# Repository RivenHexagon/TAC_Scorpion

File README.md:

# TAC_Scorpion
## Mixing Console S1100 Channel Modification

This modification **splits** the TAC Scorpion **S1100** channel **modules** into three **groups** and **modifies** them accordingly:

*   **Group 1**: AML-16-007 ***Mic Input*** Modification<br>
    <http://www.audiomaintenance.com/acatalog/AML-16-007_extended_info.html>
*   **Group 2**: AML-16-004 ***Line Input*** Modification<br>
    <http://www.audiomaintenance.com/acatalog/AML-16-004_extended_info.html>
*   **Group 3**: SK25 ***Descrete Op-Amp*** (DOA) Modification<br>
    <https://www.soundskulptor.com/en/proddetail.php?prod=SK25>

### New Circuit Diagrams
For each modification the **circuit diagram** of the **S1100** module (PBC GL270D) is **redrawn**, reflecting the changes made.

### New Connector Cards
Further more, all **connector cards** are **redesigned**, providing a single layer **PCB layout** for **DIY** manuafcturing. It has slight improvements and allowes for the replacement of old **corroded** connectors with **new** gold plated components.

### This Repo
This repository provides all the **design resources** created for this project. The majority of the modifications are **based** on the reverse engineering of the above linked **Audio Maintenance Limited** products and the **Sound Sculptor** kit.

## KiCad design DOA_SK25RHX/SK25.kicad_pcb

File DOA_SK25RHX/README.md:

## Soundskulptor SK 25
<https://www.soundskulptor.com/en/proddetail.php?prod=SK25>
The SK25 Descrete OpAmp module is redesigned with our own layout for DIY process.

### AMEK/TAC Scorpion 2520 Differential Mod

<https://www.pcbway.com/project/share/AMEK_TAC_Scorpion_2520_Differential_Mod___.html>

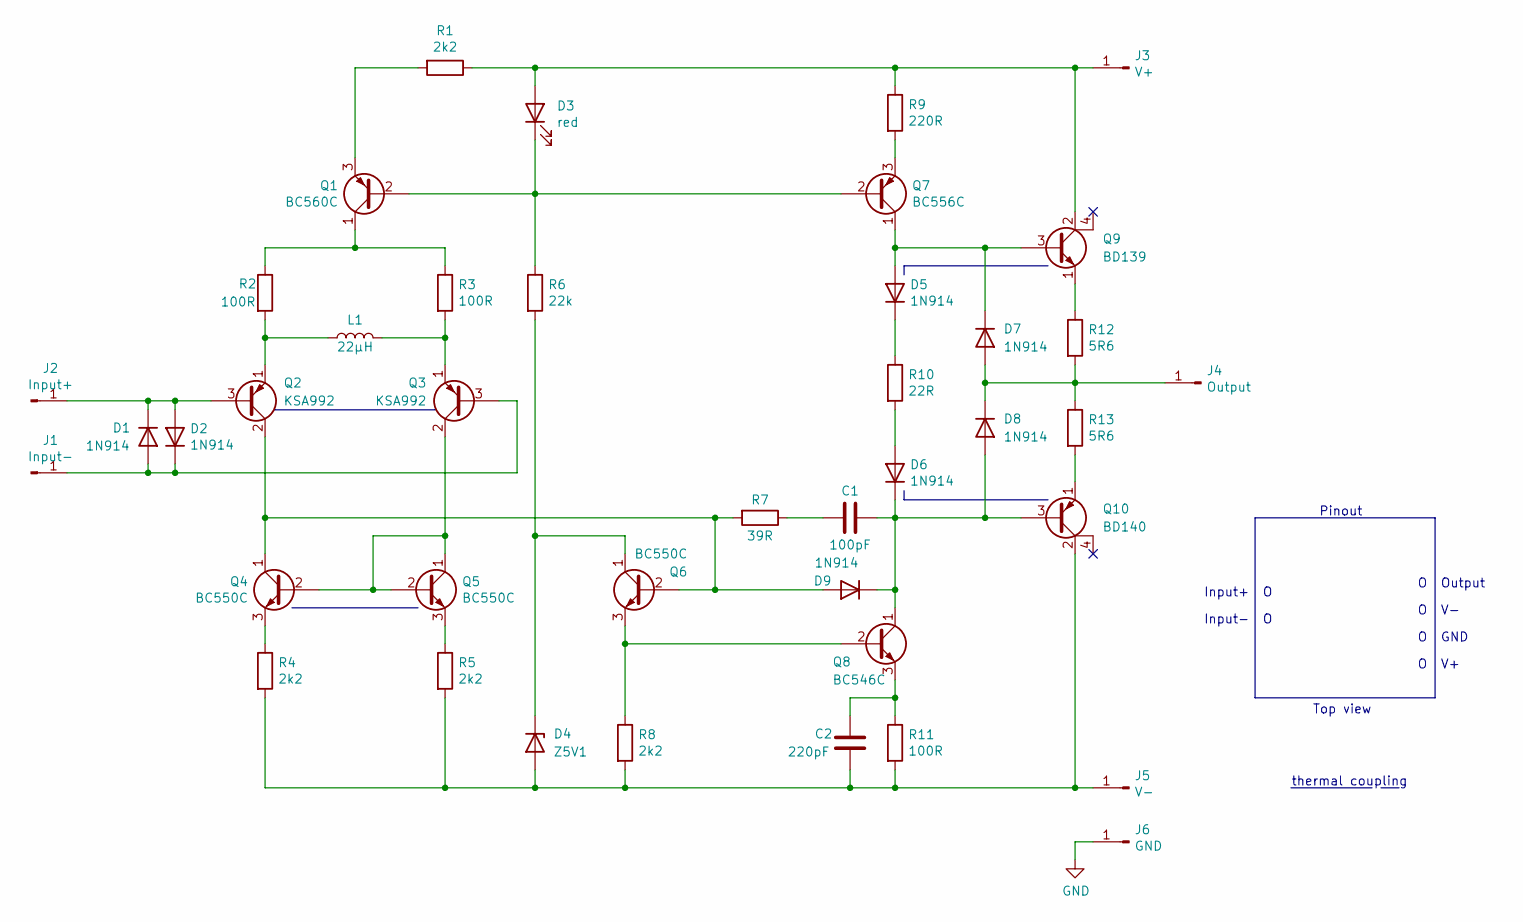
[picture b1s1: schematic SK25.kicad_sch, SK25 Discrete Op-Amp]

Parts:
C1: 100pF; C_Disc_D5.0mm_W2.5mm_P2.50mm
C2: 220pF; C_Disc_D5.0mm_W2.5mm_P2.50mm
D1, D2, D7, D8, D9: 1N914; D_DO-35_SOD27_P2.54mm_Vertical_KathodeUp
D3: red; LED_D3.0mm
D4: Z5V1; D_DO-35_SOD27_P2.54mm_Vertical_AnodeUp
D5, D6: 1N914; D_DO-35_SOD27_P10.16mm_Horizontal
J1: Input-; Pin_D1.1mm_L8.5mm_W2.5mm_FlatFork
J2: Input+; Pin_D1.1mm_L8.5mm_W2.5mm_FlatFork
J3: V+; Pin_D1.1mm_L8.5mm_W2.5mm_FlatFork
J4: Output; Pin_D1.1mm_L8.5mm_W2.5mm_FlatFork
J5: V-; Pin_D1.1mm_L8.5mm_W2.5mm_FlatFork
J6: GND; Pin_D1.1mm_L8.5mm_W2.5mm_FlatFork
L1: 22µH; L_Axial_L6.6mm_D2.7mm_P2.54mm_Vertical_Vishay_IM-2
Q1: BC560C; TO-92
Q2, Q3: KSA992; TO-92
Q4, Q5, Q6: BC550C; TO-92
Q7: BC556C; TO-92
Q8: BC546C; TO-92
Q9: BD139; to225_std
Q10: BD140; to225_std
R1, R4, R5, R8: 2k2; R_Axial_DIN0207_L6.3mm_D2.5mm_P2.54mm_Vertical
R2, R3, R11: 100R; R_Axial_DIN0207_L6.3mm_D2.5mm_P2.54mm_Vertical
R6: 22k; R_Axial_DIN0207_L6.3mm_D2.5mm_P2.54mm_Vertical
R7: 39R; R_Axial_DIN0207_L6.3mm_D2.5mm_P2.54mm_Vertical
R9: 220R; R_Axial_DIN0207_L6.3mm_D2.5mm_P2.54mm_Vertical
R10: 22R; R_Axial_DIN0207_L6.3mm_D2.5mm_P2.54mm_Vertical
R12, R13: 5R6; R_Axial_DIN0207_L6.3mm_D2.5mm_P2.54mm_Vertical

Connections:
GND: J6.1
unnamed: C1.1, D6.1 (K), D8.2 (A), D9.1 (K), Q8.1 (C), Q10.3 (B)
unnamed: C1.2, R7.1
unnamed: C2.1, Q8.3 (E), R11.1
unnamed: C2.2, D4.2 (A), J5.1, Q10.2 (C), R4.2, R5.2, R8.2, R11.2
unnamed: D1.1 (K), D2.2 (A), J2.1, Q2.3 (B)
unnamed: D1.2 (A), D2.1 (K), J1.1, Q3.3 (B)
unnamed: D3.1 (K), Q1.2 (B), Q7.2 (B), R6.1
unnamed: D3.2 (A), J3.1, Q9.2 (C), R1.1, R9.1
unnamed: D4.1 (K), Q6.1 (C), R6.2
unnamed: D5.1 (K), R10.1
unnamed: D5.2 (A), D7.1 (K), Q7.1 (C), Q9.3 (B)
unnamed: D6.2 (A), R10.2
unnamed: D7.2 (A), D8.1 (K), J4.1, R12.2, R13.1
unnamed: D9.2 (A), Q2.2 (C), Q4.1 (C), Q6.2 (B), R7.2
unnamed: L1.1, Q2.1 (E), R2.2
unnamed: L1.2, Q3.1 (E), R3.2
unnamed: Q1.1 (C), R2.1, R3.1
unnamed: Q1.3 (E), R1.2
unnamed: Q3.2 (C), Q4.2 (B), Q5.1 (C), Q5.2 (B)
unnamed: Q4.3 (E), R4.1
unnamed: Q5.3 (E), R5.1
unnamed: Q6.3 (E), Q8.2 (B), R8.1
unnamed: Q7.3 (E), R9.2
unnamed: Q9.1 (E), R12.1
unnamed: Q10.1 (E), R13.2

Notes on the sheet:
Top view
thermal coupling
Pinout
O V-
Input- O
Input+ O
O V+
O GND
O Output

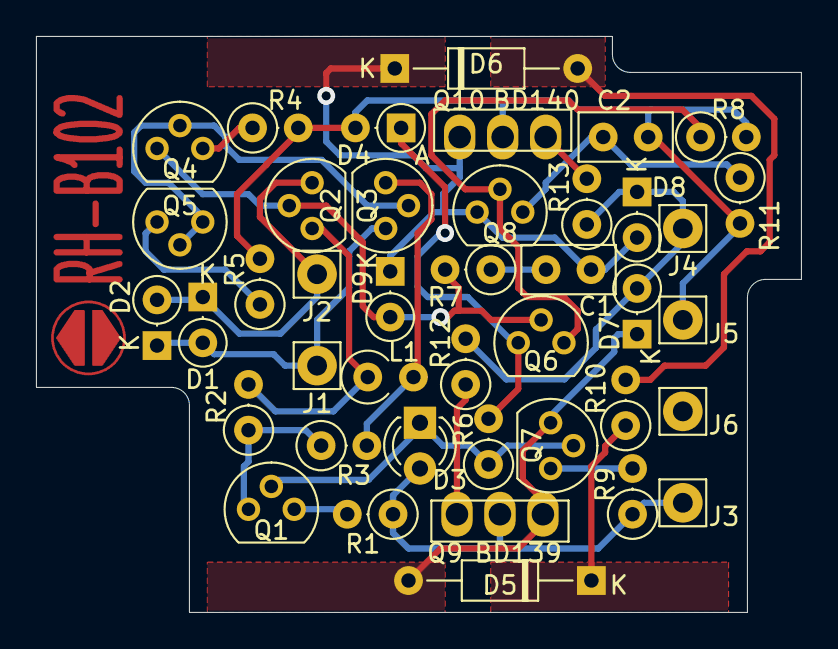
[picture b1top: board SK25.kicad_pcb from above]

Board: 2 copper layers, 42.5 x 32.0 mm, 41 parts (0 on the bottom side), 25 nets.

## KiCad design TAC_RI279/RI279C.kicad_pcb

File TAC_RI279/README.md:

# Total Audio Concepts (TAC) Scorpion Mixing Console Overhaul
## PCB RI279

Redesign of the Bus Connector Card (PCB RI279) in order to populate it
with gold plated Audio Jacks. I made 8 of them fit a copper plated Eurocard
(100 mm x 80 mm) substrate for DIY etching.

## Made With

I named the new version RI279C and made them with KiCad 5.1.7. using a git
submodule that handles any special footprints:

https://github.com/RivenHexagon/TAC_KiCad_lib.git

## Further Modifications

The XLR Bus Out connectors were panel mounted and solder wired to the PCB as
well as the Tape Return wiring harness. I've provided two 3-pin Molex connectors
and a 2-pole pin header (GND and signal) for the wire ging out to the vu-meter.

Mirrored image of the original PCB:

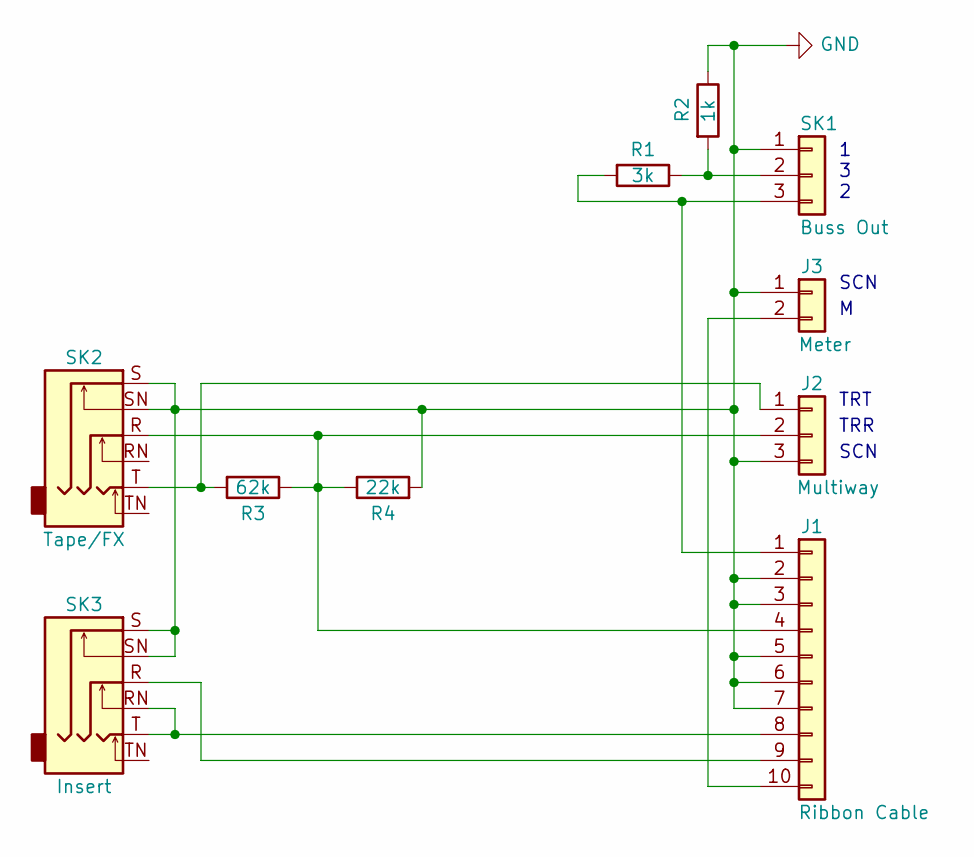
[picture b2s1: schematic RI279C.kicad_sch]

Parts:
J1: Ribbon Cable; Molex_KK-254_AE-6410-10A_1x10_P2.54mm_Vertical
J2: Multiway; Molex_KK-254_AE-6410-03A_1x03_P2.54mm_Vertical
J3: Meter; PinHeader_1x02_P2.54mm_Vertical
R1: 3k; R_Axial_DIN0207_L6.3mm_D2.5mm_P10.16mm_Horizontal
R2: 1k; R_Axial_DIN0207_L6.3mm_D2.5mm_P10.16mm_Horizontal
R3: 62k; R_Axial_DIN0207_L6.3mm_D2.5mm_P10.16mm_Horizontal
R4: 22k; R_Axial_DIN0207_L6.3mm_D2.5mm_P10.16mm_Horizontal
SK1: Buss Out; Molex_KK-254_AE-6410-03A_1x03_P2.54mm_Vertical
SK2: Tape/FX; CL13345
SK3: Insert; CL13345

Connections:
GND: J1.2, J1.3, J1.5, J1.6, J1.7, J2.3, J3.1, R2.1, R4.2, SK1.1, SK2.S, SK2.SN, SK3.S, SK3.SN
unnamed: J1.1, R1.2, SK1.3
unnamed: J1.4, J2.2, R3.1, R4.1, SK2.R
unnamed: J1.8, SK3.RN, SK3.T
unnamed: J1.9, SK3.R
unnamed: J1.10, J3.2
unnamed: J2.1, R3.2, SK2.T
unnamed: R1.1, R2.2, SK1.2

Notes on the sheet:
TRT
1 3 2
SCN
TRR

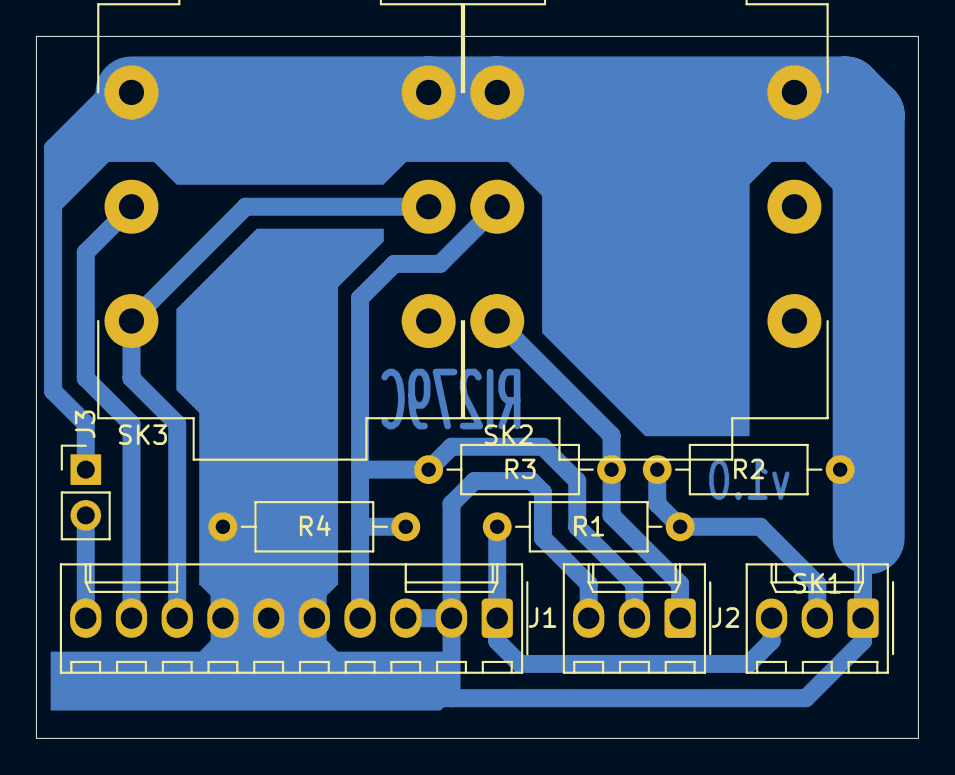
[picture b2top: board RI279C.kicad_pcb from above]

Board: 2 copper layers, 49.0 x 39.0 mm, 10 parts (0 on the bottom side), 8 nets.

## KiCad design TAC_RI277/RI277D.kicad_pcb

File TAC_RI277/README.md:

# Total Audio Concepts (TAC) Scorpion Mixing Console Overhaul
## PCB RI277

Redesign of the Input Connector Card (PCB RI277) in order to populate it
with gold plated Audio Jacks. I made 6 of them fit a copper plated Eurocard
(100 mm x 80 mm) substrate for DIY etching.

## Made With

I named the new version RI277D and made them with KiCad 5.1.7. using a git
submodule that handles any special footprints:

https://github.com/RivenHexagon/TAC_KiCad_lib.git

## Further Modifications

The XLR Bus Out connectors were panel mounted and solder wired to the PCB as
well as the Tape Return wiring harness. I've provided two 3-pin Molex connectors
instead.

Mirrored image of the original PCB:

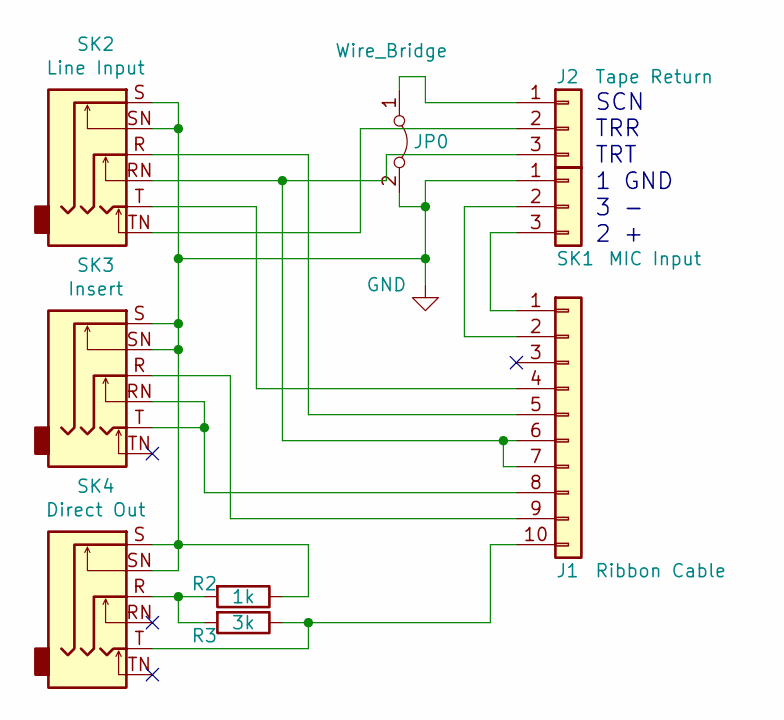
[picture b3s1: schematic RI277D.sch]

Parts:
J1: Ribbon Cable; Molex_KK-254_AE-6410-10A_1x10_P2.54mm_Vertical
J2: Tape Return; Molex_KK-254_AE-6410-03A_1x03_P2.54mm_Vertical
JP0: Wire_Bridge; Wire_Bridge_P10.16mm_Horizontal
R2: 1k; R_Axial_DIN0207_L6.3mm_D2.5mm_P10.16mm_Horizontal
R3: 3k; R_Axial_DIN0207_L6.3mm_D2.5mm_P10.16mm_Horizontal
SK1: MIC Input; Molex_KK-254_AE-6410-03A_1x03_P2.54mm_Vertical
SK2: Line Input; CL13345
SK3: Insert; CL13345
SK4: Direct Out; CL13345

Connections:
GND: JP0.2 (B), R2.1, SK1.1, SK2.S, SK2.SN, SK3.S, SK3.SN, SK4.S, SK4.SN
unnamed: J1.1, SK1.3
unnamed: J1.2, SK1.2
unnamed: J1.4, SK2.T
unnamed: J1.5, SK2.R
unnamed: J1.6, J1.7, J2.3, SK2.RN
unnamed: J1.8, SK3.RN, SK3.T
unnamed: J1.9, SK3.R
unnamed: J1.10, R3.1, SK4.T
unnamed: J2.1, JP0.1 (A)
unnamed: J2.2, SK2.TN
unnamed: R2.2, R3.2, SK4.R

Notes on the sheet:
SCN TRR TRT 1 GND 3 - 2 +

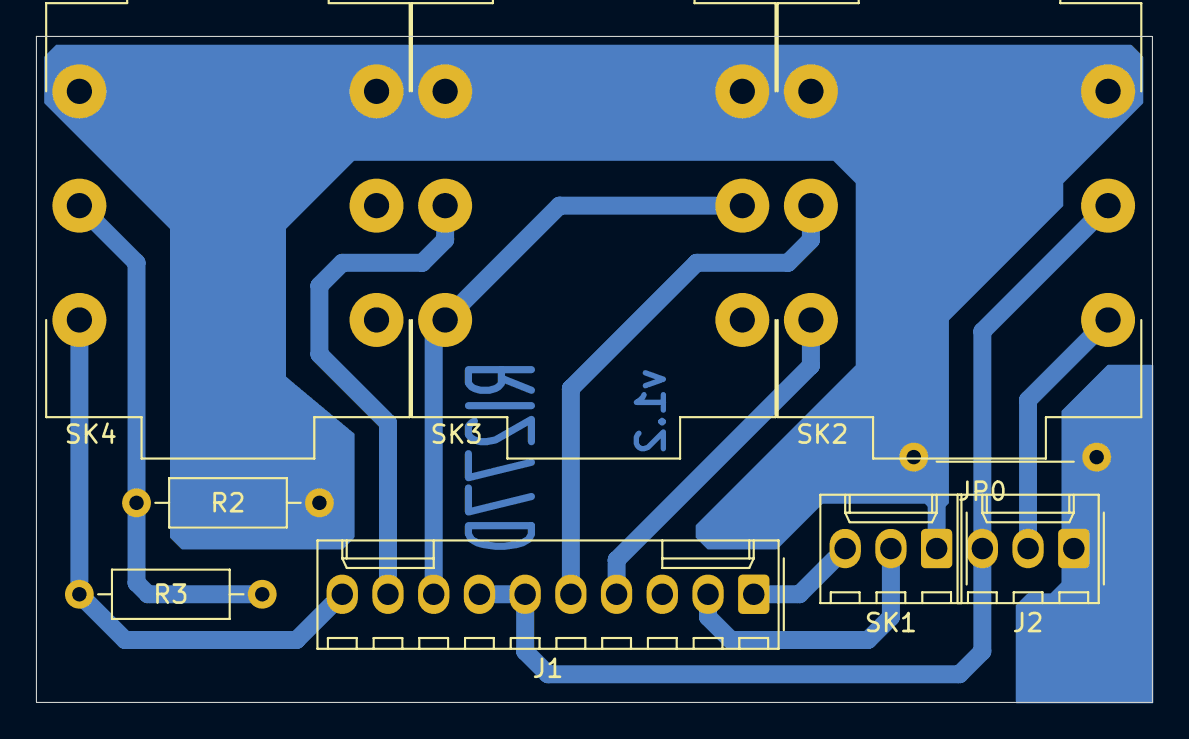
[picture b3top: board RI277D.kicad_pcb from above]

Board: 2 copper layers, 62.0 x 37.0 mm, 9 parts (0 on the bottom side), 12 nets.

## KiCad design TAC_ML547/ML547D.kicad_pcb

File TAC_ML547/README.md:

# Total Audio Concepts (TAC) Scorpion Mixing Console Overhaul
## PCB ML547

Redesign of the Input/Insert Connector Card (PCB ML547) in order to populate it
with gold plated Audio Jacks. The original dimensions are 100 mm x 40 mm. Only
two of them where installed in my TAC scorpion, hence two layouts fit half a
copper plated Eurocard (100 mm x 80 mm) substrate for DIY etching.

## Made With

I named the new version ML547D and made them with KiCad 5.1.7. using a git
submodule that handles any special footprints:

https://github.com/RivenHexagon/TAC_KiCad_lib.git

## Further Modifications

One copper trace of the old layout follows a very narrow path between two pins
of the left and right insert jacks (highlighted in the mirrored PCB image). The
new layout provides this connection with a trace on the top layer. For my single
layer DIY substrate I've used a simple wire.

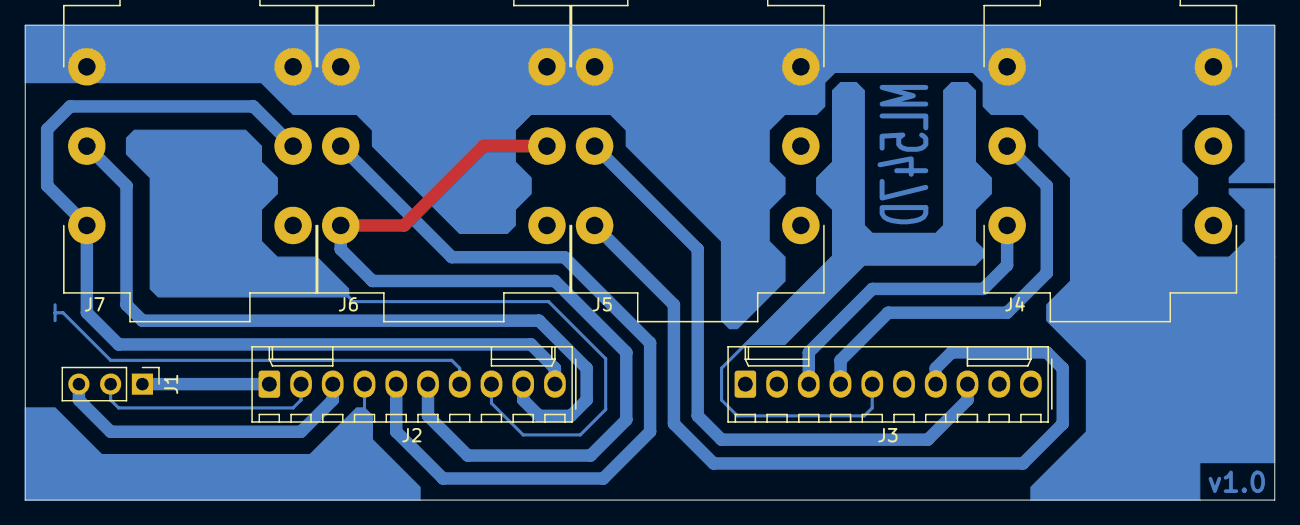
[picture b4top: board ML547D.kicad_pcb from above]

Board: 2 copper layers, 100.0 x 38.0 mm, 7 parts (0 on the bottom side), 12 nets.

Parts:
J1: Direct Out; PinHeader_1x03_P2.54mm_Vertical
J2, J3: Ribbon; Molex_KK-254_AE-6410-10A_1x10_P2.54mm_Vertical_reversed
J4: Input R; CL13345
J5: Input L; CL13345
J6: Insert R; CL13345
J7: Insert L; CL13345

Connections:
unnamed: J1.1, J2.1
unnamed: J1.2, J2.2
unnamed: J1.3, J2.3
unnamed: J2.5, J6.R
unnamed: J2.6, J6.RN, J6.T
unnamed: J2.9, J7.R
unnamed: J2.10, J7.RN, J7.T
unnamed: J3.3, J4.T
unnamed: J3.4, J4.R
unnamed: J3.7, J5.T
unnamed: J3.8, J5.R
unnamed: J4.S, J4.SN, J5.S, J5.SN, J6.S, J6.SN, J7.S, J7.SN

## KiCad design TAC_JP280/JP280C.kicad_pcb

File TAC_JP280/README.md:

# Total Audio Concepts (TAC) Scorpion Mixing Console Overhaul
## PCB JP280

Redesign of Monitor Connector Card (PCB JP280) in order to populate it with gold
plated Audio Jacks and Molex connectors. The original PCB exceeds the dimensions
of an Eurocard (100 mm x 160 mm) substrate. Luckily it's possible to split it up
into two independet parts, so the layouts can be placed on a copper-plated blank
and etched in a DIY process (see mirrored image of original PCB).

## Made With

I named the new versions JP280C1 & JP280C2 and made them with KiCad 5.1.7. using
a git submodule that handles any special footprints:

https://github.com/RivenHexagon/TAC_KiCad_lib.git

## Further Modifications

The XLR/audio jacks SK1 - SK4 are mounted to the back panel and were then solder
wired to the PCB. The solder connections have now been replaced with 3-pin Molex
connectors.

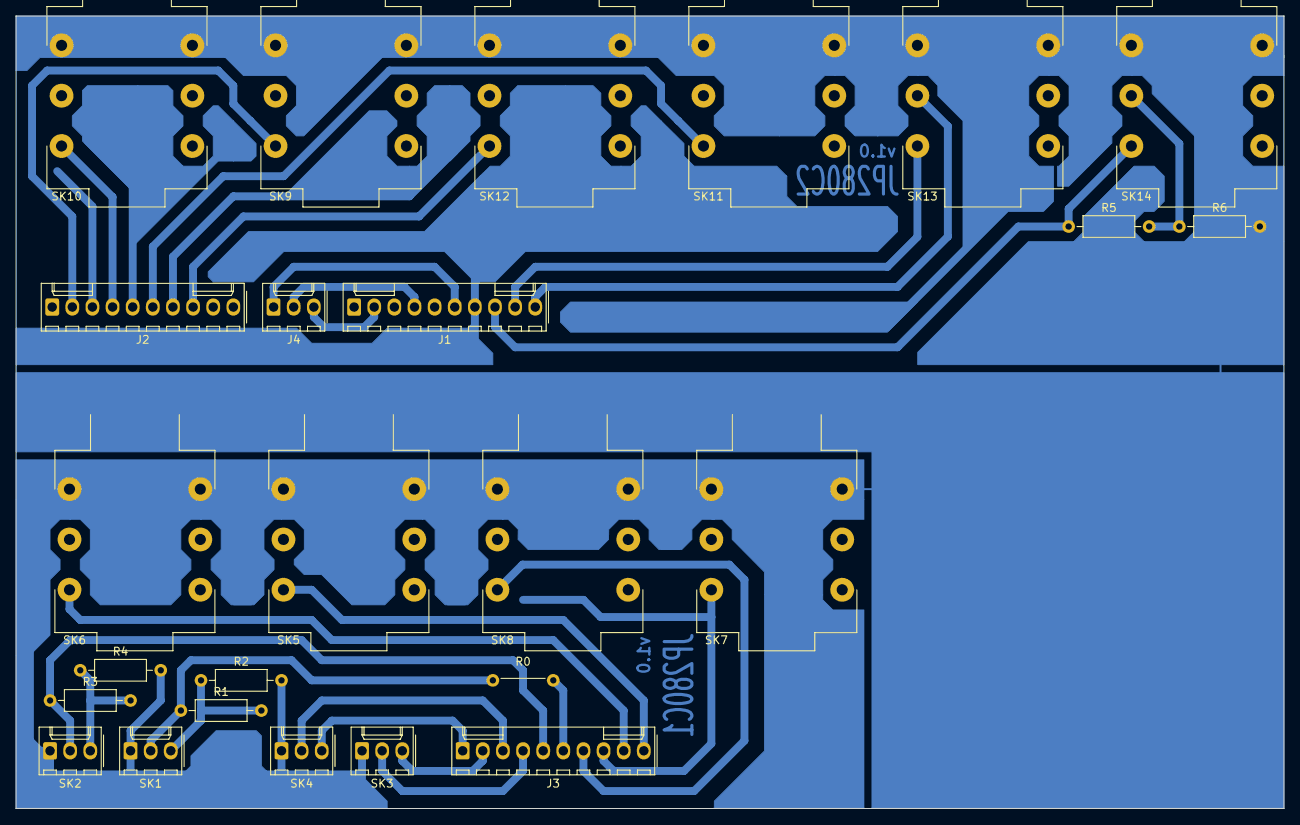
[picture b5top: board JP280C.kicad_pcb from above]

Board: 2 copper layers, 160.0 x 100.0 mm, 25 parts (0 on the bottom side), 25 nets.

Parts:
J1: Ribbon Cable (A); Molex_KK-254_AE-6410-10A_1x10_P2.54mm_Vertical_reversed
J2: Ribbon Cable (B); Molex_KK-254_AE-6410-10A_1x10_P2.54mm_Vertical_reversed
J3: Ribbon Cable (C); Molex_KK-254_AE-6410-10A_1x10_P2.54mm_Vertical_reversed
J4: Meters; Molex_KK-254_AE-6410-03A_1x03_P2.54mm_Vertical_reversed
R0: 0R; Wire_Bridge_P7.62mm_Horizontal
R1, R3: 3k; R_Axial_DIN0207_L6.3mm_D2.5mm_P10.16mm_Horizontal
R2, R4: 1k; R_Axial_DIN0207_L6.3mm_D2.5mm_P10.16mm_Horizontal
R5: 10k; R_Axial_DIN0207_L6.3mm_D2.5mm_P10.16mm_Horizontal
R6: 10R; R_Axial_DIN0207_L6.3mm_D2.5mm_P10.16mm_Horizontal
SK1: Left Bus; Molex_KK-254_AE-6410-03A_1x03_P2.54mm_Vertical_reversed
SK2: Right Bus; Molex_KK-254_AE-6410-03A_1x03_P2.54mm_Vertical_reversed
SK3: Left Insert; Molex_KK-254_AE-6410-03A_1x03_P2.54mm_Vertical_reversed
SK4: Right Insert; Molex_KK-254_AE-6410-03A_1x03_P2.54mm_Vertical_reversed
SK5: Left Monitor; CL13345
SK6: Right Monitor; CL13345
SK7: Left Aux Monitor; CL13345
SK8: Right Aux Monitor; CL13345
SK9: Left Tape 2; CL13345
SK10: Right Tape 2; CL13345
SK11: Left Tape 1; CL13345
SK12: Right Tape 1; CL13345
SK13: Talkback; CL13345
SK14: OSC; CL13345

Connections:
GND: R2.2, R4.2, R6.2, SK1.1, SK2.1, SK3.1, SK4.1, SK5.S, SK5.SN, SK6.S, SK6.SN, SK7.S, SK7.SN, SK8.S, SK8.SN, SK9.S, SK9.SN, SK10.S, SK10.SN, SK11.S, SK11.SN, SK12.S, SK12.SN, SK13.S, SK13.SN, SK14.S, SK14.SN
unnamed: J1.2, J4.3
unnamed: J1.4, J4.2
unnamed: J1.6, J4.1
unnamed: J1.8, R5.1, SK14.T
unnamed: J1.9, SK13.T
unnamed: J1.10, SK13.R
unnamed: J2.2, SK9.T
unnamed: J2.4, SK10.T
unnamed: J2.6, SK11.T
unnamed: J2.8, SK12.T
unnamed: J3.1, SK4.3
unnamed: J3.2, SK3.3
unnamed: J3.3, SK4.2
unnamed: J3.4, SK3.2
unnamed: J3.5, R3.1, SK2.2
unnamed: J3.6, R0.2
unnamed: J3.7, SK8.T
unnamed: J3.8, SK7.T
unnamed: J3.9, SK6.T
unnamed: J3.10, SK5.T
unnamed: R0.1, R1.1, SK1.2
unnamed: R1.2, R2.1, SK1.3
unnamed: R3.2, R4.1, SK2.3
unnamed: R5.2, R6.1, SK14.R

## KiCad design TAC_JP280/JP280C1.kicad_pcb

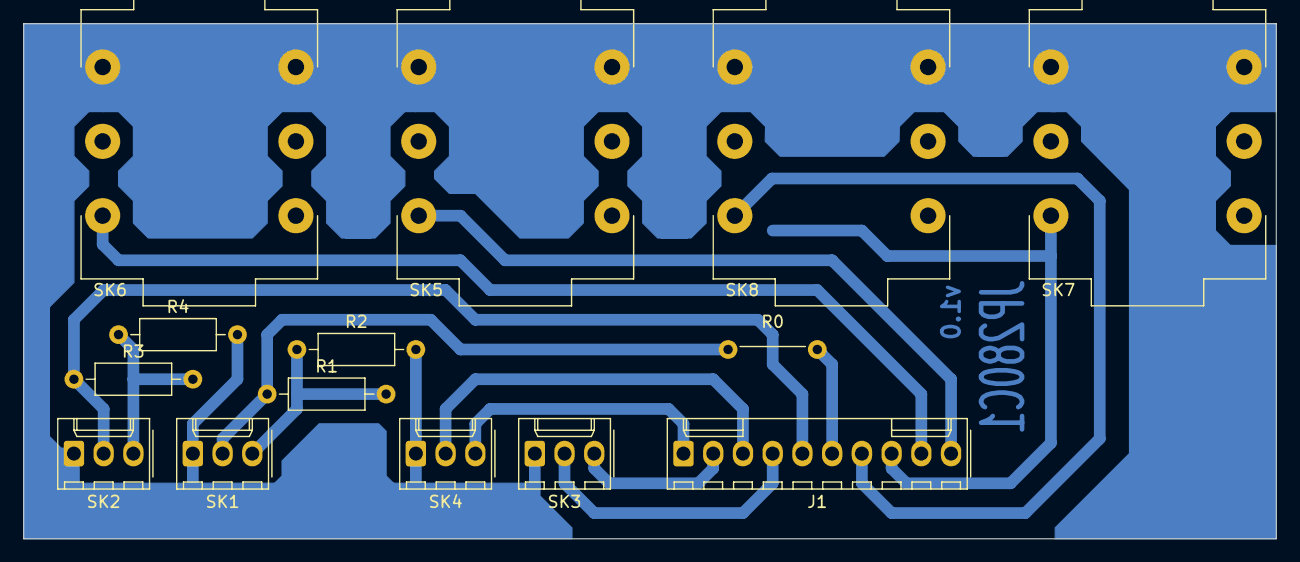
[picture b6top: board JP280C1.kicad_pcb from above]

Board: 2 copper layers, 107.0 x 44.0 mm, 14 parts (0 on the bottom side), 14 nets.

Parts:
J1: Ribbon Cable (C); Molex_KK-254_AE-6410-10A_1x10_P2.54mm_Vertical_reversed
R0: 0R; Wire_Bridge_P7.62mm_Horizontal
R1, R3: 3k; R_Axial_DIN0207_L6.3mm_D2.5mm_P10.16mm_Horizontal
R2, R4: 1k; R_Axial_DIN0207_L6.3mm_D2.5mm_P10.16mm_Horizontal
SK1: Left Bus; Molex_KK-254_AE-6410-03A_1x03_P2.54mm_Vertical_reversed
SK2: Right Bus; Molex_KK-254_AE-6410-03A_1x03_P2.54mm_Vertical_reversed
SK3: Left Insert; Molex_KK-254_AE-6410-03A_1x03_P2.54mm_Vertical_reversed
SK4: Right Insert; Molex_KK-254_AE-6410-03A_1x03_P2.54mm_Vertical_reversed
SK5: Left Monitor; CL13345
SK6: Right Monitor; CL13345
SK7: Left Aux Monitor; CL13345
SK8: Right Aux Monitor; CL13345

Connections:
GND: R2.2, R4.2, SK1.1, SK2.1, SK3.1, SK4.1, SK5.S, SK5.SN, SK6.S, SK6.SN, SK7.S, SK7.SN, SK8.S, SK8.SN
unnamed: J1.1, SK4.3
unnamed: J1.2, SK3.3
unnamed: J1.3, SK4.2
unnamed: J1.4, SK3.2
unnamed: J1.5, R3.1, SK2.2
unnamed: J1.6, R0.2
unnamed: J1.7, SK8.T
unnamed: J1.8, SK7.T
unnamed: J1.9, SK6.T
unnamed: J1.10, SK5.T
unnamed: R0.1, R1.1, SK1.2
unnamed: R1.2, R2.1, SK1.3
unnamed: R3.2, R4.1, SK2.3

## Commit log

2022-07-01 Merged all TAC related repositories into this new one.
2022-07-01 input section of S1000
2022-07-01 fixed untracked
2022-07-02 fix in MicIn schematic, BJT section of S1000
2022-07-02 fully drawn components of MicIn mod PCB AML-07-048
2022-07-02 renamed components of AML pcb section, started drawing Eq section
2022-07-03 Eq middle section
2022-07-03 completed EQ section
2022-07-03 included RI277 to diagram, fixed missing bridge pin 6-7 on RI277D
2022-07-03 diagram makeup, updated readme
2022-07-03 typos
2022-07-20 completed overload and part of PFL switching section
2022-07-21 completed PAN section and S1100 aux send option
2022-07-21 completed switching section. Have to revise pin and resistor accociation
2022-07-22 revised pin assignment DIN 8-12. Need to verify DIN 13-20
2022-07-24 completed MicIn diagram
2022-07-24 renamed LineIn jumpers, image cleanup
2022-07-29 completed MicIn and LineIn circuit diagrams and fixed errors.
2022-07-31 DOA readme
2022-08-04 completed foot print assignment for DOA SK25
2022-08-05 crude placement
2022-11-17 abandoned layout. just TAC schematics for DOA socket
2023-01-16 updated .gitignore for KiCad 6
2023-01-16 status before using KiCad 6.0
2023-01-16 expanded PBC borders to fit with TAC 270D mod clearance
2023-01-23 complete plausible placement
2023-01-23 added PCB serial No
2023-01-23 2/3 of routing
2023-01-23 completed routing, except diose pads
2023-01-24 completed routing, added solder pads and solder mask clearance
2023-01-25 small adjustments
2023-01-25 uses copper fill zones
2023-01-25 modified BJT footprints
2023-01-25 generated gerber files
2023-01-26 fixed Mask position
2023-01-26 created gbr files
2023-02-25 created BOM
2023-12-26 created new KiCad project for DOA circuit in separate folder
2023-12-30 first iteration DOA Mod circuit diagram
2024-07-06 DOA SK25 manufacturing files
